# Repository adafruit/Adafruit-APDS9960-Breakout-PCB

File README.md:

## Adafruit APDS9960 Breakout PCB

<a href="http://www.adafruit.com/products/3595"><br/>
Click here to purchase one from the Adafruit shop</a>

PCB files for the Adafruit APDS9960 IR gesture, proximity, RGB, ambient light sensor breakout board

Format is EagleCAD schematic and board layout

For more details, check out the product page at
* https://www.adafruit.com/products/3595

### Description

This breakout is chock full o' sensors! Add basic gesture sensing, RGB color sensing, proximity sensing, or ambient light sensing to your project with the Adafruit APDS9960 Proximity, Light, RGB and Gesture Sensor. When connected to your microcontroller (running our library code) it can detect simple gestures (left to right, right to left, up to down, down to up are currently supported), return the amount of red, blue, green, and clear light, or return how close an object is to the front of the sensor. This device uses an I2C interface so it's easy to wire up and use.

The APDS9960 from Avago Technologies has an integrated IR LED and driver, along with four directional photodiodes that sense reflected IR energy from the LED. It's proximity detection feature allows it to measure the distance an object is from the front of the sensor (up to a few centimeters) with 8 bit resolution.

Since there are four IR sensors, you can measure the changes in light reflectance at each of the cardinal locations over time and turn those changes into gestures. Our interface library can detect directional gestures (left to right, right to left, up to down, down to up), but in theory more complicated gestures like zig-zag, clockwise or counterclockwise circle, near to far, etc. could also be detected with additional code.

The APDS9960 has a configurable interrupt that can fire when a certain proximity threshold is broken, or when a color sensor breaks a certain threshold.

For your convenience we've pick-and-placed the sensor on a PCB with a 3.3V regulator and some level shifting so it can be easily used with your favorite 3.3V or 5V microcontroller.

### License

Adafruit invests time and resources providing this open source design, please support Adafruit and open-source hardware by purchasing products from [Adafruit](https://www.adafruit.com)!

Designed by Limor Fried/Ladyada for Adafruit Industries.

Creative Commons Attribution/Share-Alike, all text above must be included in any redistribution. See license.txt for additional details.

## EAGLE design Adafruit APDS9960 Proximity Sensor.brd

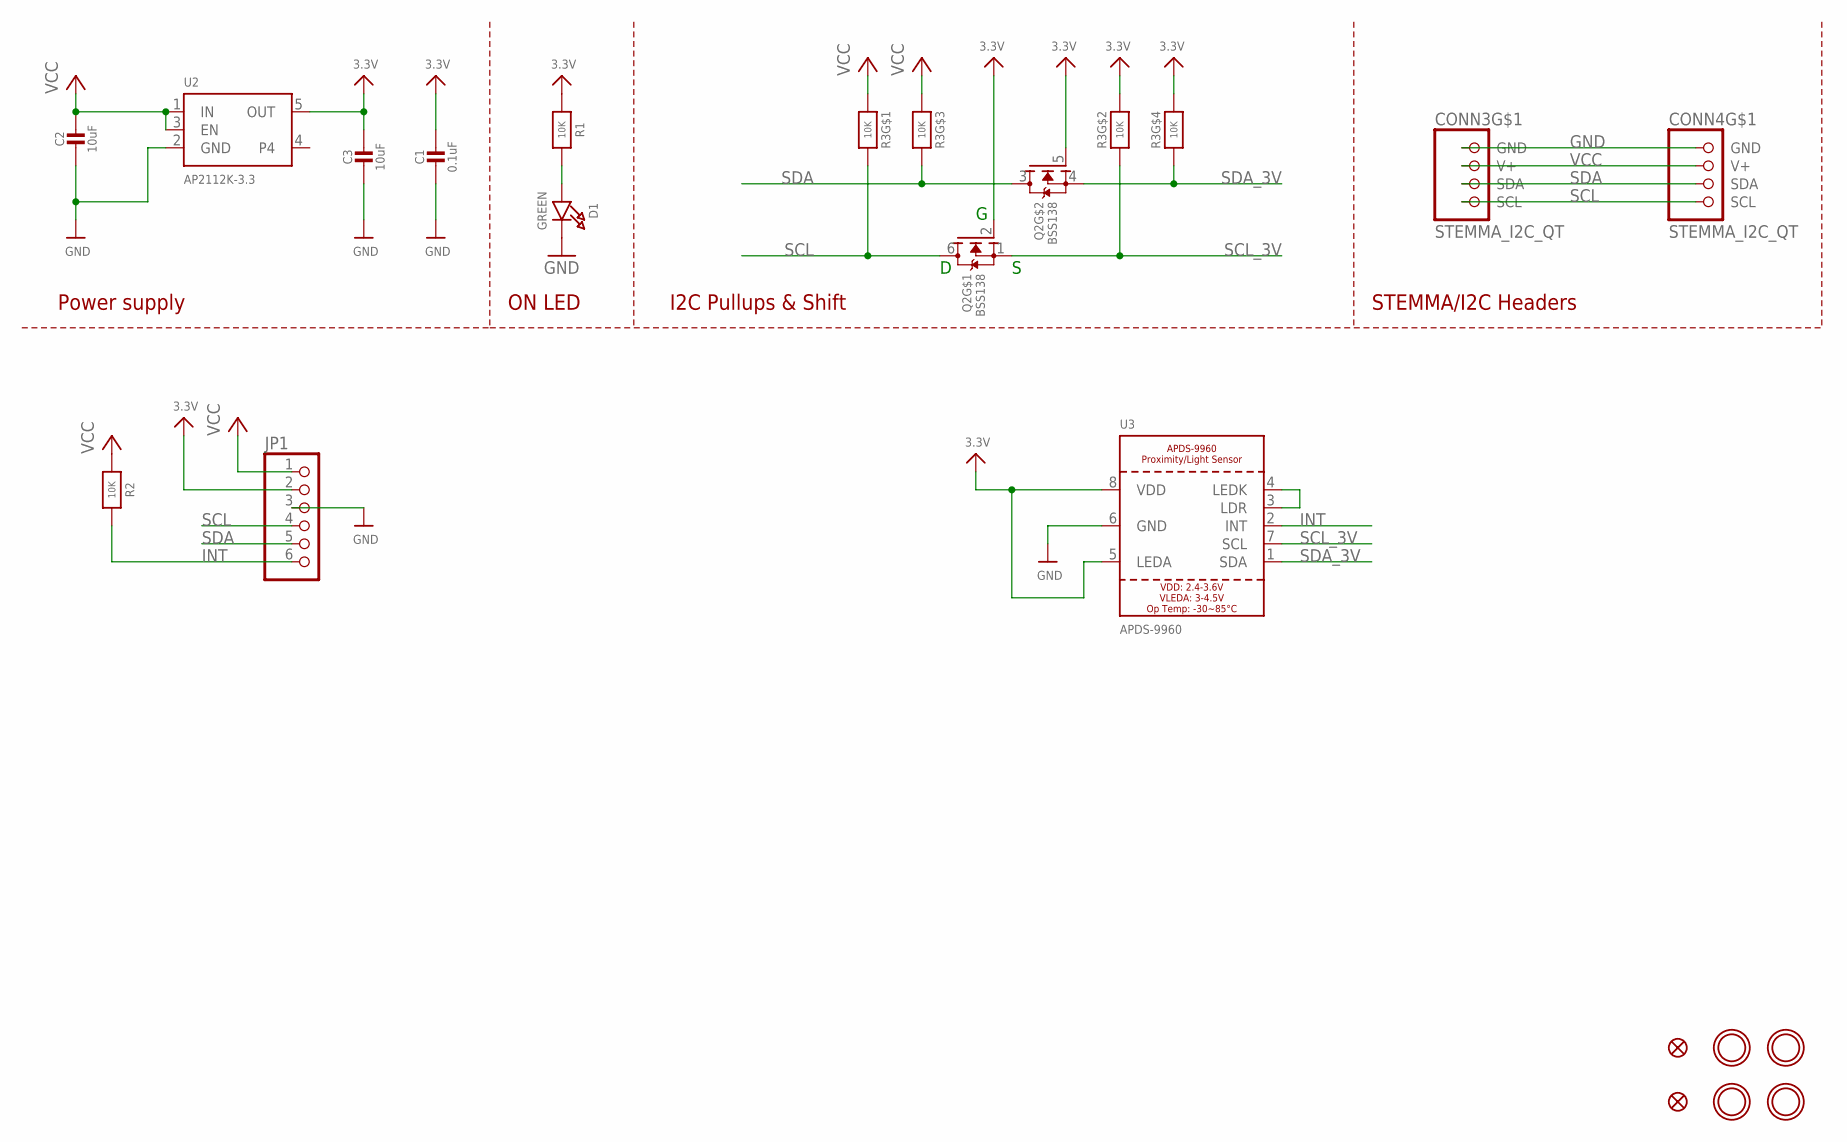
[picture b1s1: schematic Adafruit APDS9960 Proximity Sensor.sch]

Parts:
C1: 0.1uF; 0603-NO
C2, C3: 10uF; 0805-NO
CONN3, CONN4: STEMMA_I2C_QT; JST_SH4
D1: GREEN; CHIPLED_0603_NOOUTLINE
FID3, FID4: FIDUCIAL_1MM
JP1: HEADER-1X670MIL; 1X06_ROUND_70
Q2: BSS138; SOT363
R1, R2: 10K; 0603-NO
R3: 10K; RESPACK_4X0603
U2: AP2112K-3.3; SOT23-5
U3: APDS-9960
U$1, U$17, U$19, U$21: MOUNTINGHOLE2.5; MOUNTINGHOLE_2.5_PLATED

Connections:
3.3V: C1.1, C3.1, JP1.2, Q2.2 (G), Q2.5 (G), R1.1, R3.2 (1), R3.4 (1), U2.5 (OUT), U3.5 (LEDA), U3.8 (VDD)
GND: C1.2, C2.2, C3.2, CONN3.1 (GND), CONN4.1 (GND), D1.C, JP1.3, U2.2 (GND), U3.6 (GND)
INT: JP1.6, R2.2, U3.2 (INT)
unnamed: D1.A, R1.2
unnamed: U3.3 (LDR), U3.4 (LEDK)
SCL: CONN3.4 (SCL), CONN4.4 (SCL), JP1.4, Q2.6 (D), R3.8 (2)
SCL_3V: Q2.1 (S), R3.7 (2), U3.7 (SCL)
SDA: CONN3.3 (SDA), CONN4.3 (SDA), JP1.5, Q2.3 (D), R3.6 (2)
SDA_3V: Q2.4 (S), R3.5 (2), U3.1 (SDA)
VCC: C2.1, CONN3.2 (V+), CONN4.2 (V+), JP1.1, R2.1, R3.1, R3.3 (1), U2.1 (IN), U2.3 (EN)

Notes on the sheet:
I2C Pullups & Shift
STEMMA/I2C Headers
ON LED
Power supply

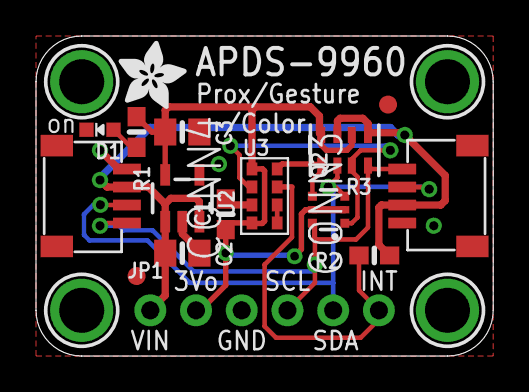
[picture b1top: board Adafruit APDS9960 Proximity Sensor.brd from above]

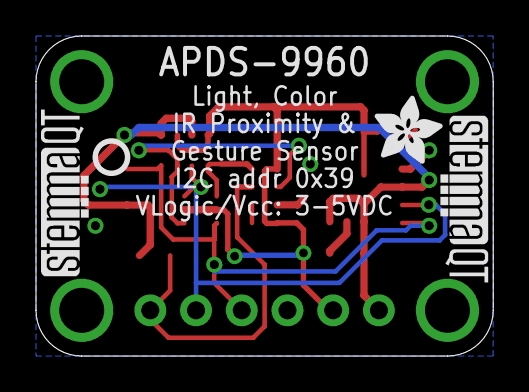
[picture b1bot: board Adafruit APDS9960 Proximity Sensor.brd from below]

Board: 2 copper layers, 25.4 x 17.8 mm, 24 parts (4 on the bottom side), 10 nets.

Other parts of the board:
U$2, U$22: ADAFRUIT_3.5MM
U$25: PCBFEAT-REV-040
U$30, U$31: STEMMAQT

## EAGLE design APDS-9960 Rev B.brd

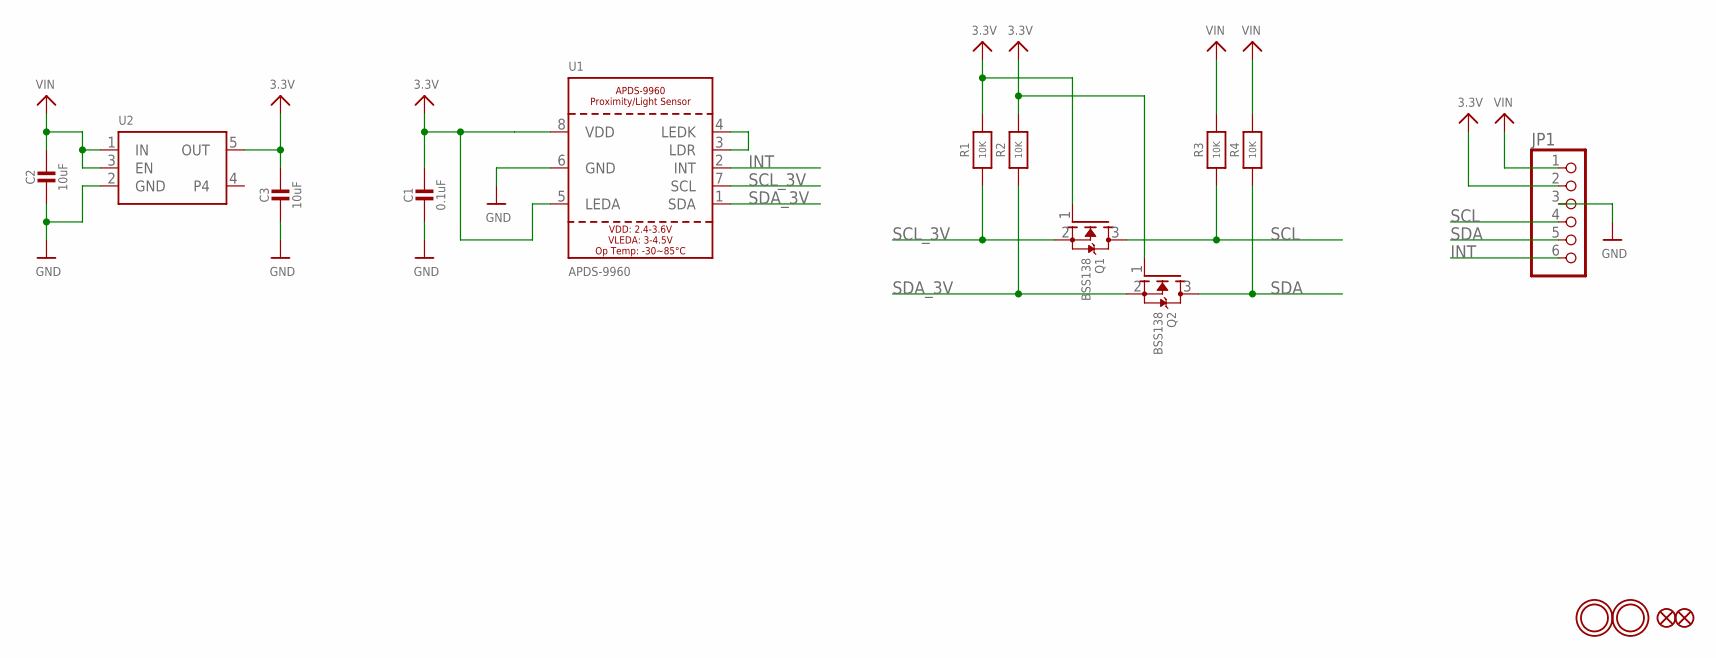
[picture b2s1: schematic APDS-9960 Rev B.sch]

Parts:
C1: 0.1uF; 0805-NO
C2, C3: 10uF; 0805-NO
FID1, FID2: FIDUCIAL_1MM
JP1: HEADER-1X676MIL; 1X06_ROUND_76
Q1, Q2: BSS138; SOT23-WIDE
R1, R2, R3, R4: 10K; 0805-NO
U1: APDS-9960
U2: VREG_SOT23-5; SOT23-5
U$1, U$2: MOUNTINGHOLE2.5; MOUNTINGHOLE_2.5_PLATED

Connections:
3.3V: C1.1, C3.1, JP1.2, Q1.1 (G), Q2.1 (G), R1.2, R2.2, U1.5 (LEDA), U1.8 (VDD), U2.5 (OUT)
GND: C1.2, C2.2, C3.2, JP1.3, U1.6 (GND), U2.2 (GND)
INT: JP1.6, U1.2 (INT)
unnamed: U1.3 (LDR), U1.4 (LEDK)
SCL: JP1.4, Q1.3 (D), R3.1
SCL_3V: Q1.2 (S), R1.1, U1.7 (SCL)
SDA: JP1.5, Q2.3 (D), R4.1
SDA_3V: Q2.2 (S), R2.1, U1.1 (SDA)
VIN: C2.1, JP1.1, R3.2, R4.2, U2.1 (IN), U2.3 (EN)

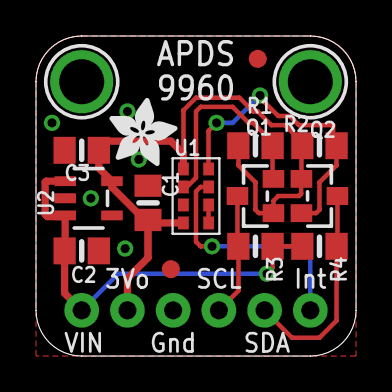
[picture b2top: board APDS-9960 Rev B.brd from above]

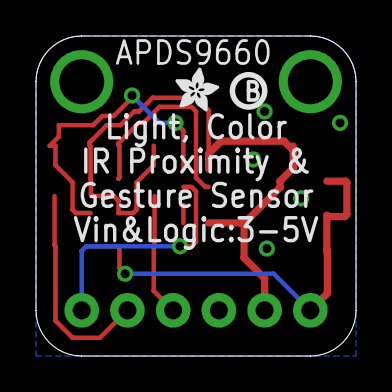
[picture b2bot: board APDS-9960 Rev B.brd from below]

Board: 2 copper layers, 17.8 x 17.8 mm, 19 parts (2 on the bottom side), 9 nets.

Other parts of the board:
U$17: PCBFEAT-REV-040
U$18: ADAFRUIT_2.5MM
U$19: ADAFRUIT_3.5MM

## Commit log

2020-03-25 Adding updated board files.

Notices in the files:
parts and their libraries:
microbuilder: This work is placed in the public domain, and may be freely used for commercial and non-commercial work with the following conditions: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
